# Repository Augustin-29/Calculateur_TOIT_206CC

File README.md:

# Calculateur TOIT 206CC (Version 1)

Ce projet open-source consiste en la rétro-ingénierie et la conception d'un calculateur de remplacement sur mesure pour la gestion du toit escamotable d'une Peugeot 206 CC. La V1 s'appuie sur une architecture matérielle moderne et un système d'exploitation temps réel pour piloter de manière fiable et sécurisée le cycle d'ouverture/fermeture du toit.

---

## 🛠️ Architecture du Projet

Le dépôt regroupe l'ensemble du projet dans une structure centralisée :
*   **`CAO/`** : Conception matérielle complète sous KiCad (Schématiques, empreintes spécifiques, modélisations 3D et fichiers de fabrication Gerber).
*   **`CODE_CT_V1/`** : Logiciel embarqué développé en C/C++ avec une structure de build basée sur CMake.

---

## 💾 Spécifications Techniques (Hardware)

Le module remplace l'électronique d'origine en modernisant la chaîne de traitement et de commande.

*   **Microcontrôleur principal** : STM32F103 (Cortex-M3), choisi pour sa gestion des périphériques et ses timers avancés nécessaires à l'acquisition des capteurs de position.
*   **Interface Véhicule & Diagnostic** : Support de la ligne K (K-line) pour la communication de diagnostic et l'analyse de protocole.
*   **Connectique d'Origine** : Intégration sur le PCB d'une empreinte sur mesure pour le connecteur jaune 26 broches spécifique au faisceau habitacle de la 206 CC.
*   **Routage & Puissance** : 
    *   Routage optimisé des pistes de puissance pour la gestion des courants des moteurs de pompe hydraulique et des actionneurs.
    *   Protection renforcée de l'étage d'alimentation face aux contraintes du réseau électrique automobile (transitoires, variations de tension).
    *   Isolation et conditionnement des signaux des micro-contacts (capteurs de fin de course des éléments du toit et du coffre).

---

## 💻 Logiciel Embarqué (Firmware)

Le code est architecturé pour garantir le déterminisme et la sécurité lors des mouvements mécaniques du toit.

*   **Système d'Exploitation** : Intégration de **FreeRTOS** pour orchestrer les tâches concurrentes (gestion de la machine d'état du toit, scrutation des capteurs, communications).
*   **Gestion de la Sécurité** : Tâches prioritaires surveillant en temps réel l'état des capteurs pour interrompre immédiatement le cycle en cas d'anomalie ou d'obstacle.
*   **Environnement de Développement** : Configuration complète sous **CMake**, facilitant la cross-compilation avec la chaîne d'outils `gcc-arm-none-eabi`.

---

## 📂 Contenu du dossier CAO

Le dossier de conception électronique inclut :
*   Le schéma structurel (`.kicad_sch`) et le routage du PCB (`.kicad_pcb`).
*   Les fichiers de fabrication indispensables (Générés dans `CAO/gerber/` : couches de cuivre, masques de soudure, sérigraphies et fichiers de perçage `.drl`).
*   Les modèles 3D des composants spécifiques (relais automobiles, connecteur jaune 26P, etc.) utilisés pour valider l'intégration mécanique de la carte dans son boîtier.

---

## 🚀 À venir (Roadmap V2)

*   Validation de la machine d'état sur banc de test et intégration véhicule.
*

---
*Projet développé par Augustin — 2026.*

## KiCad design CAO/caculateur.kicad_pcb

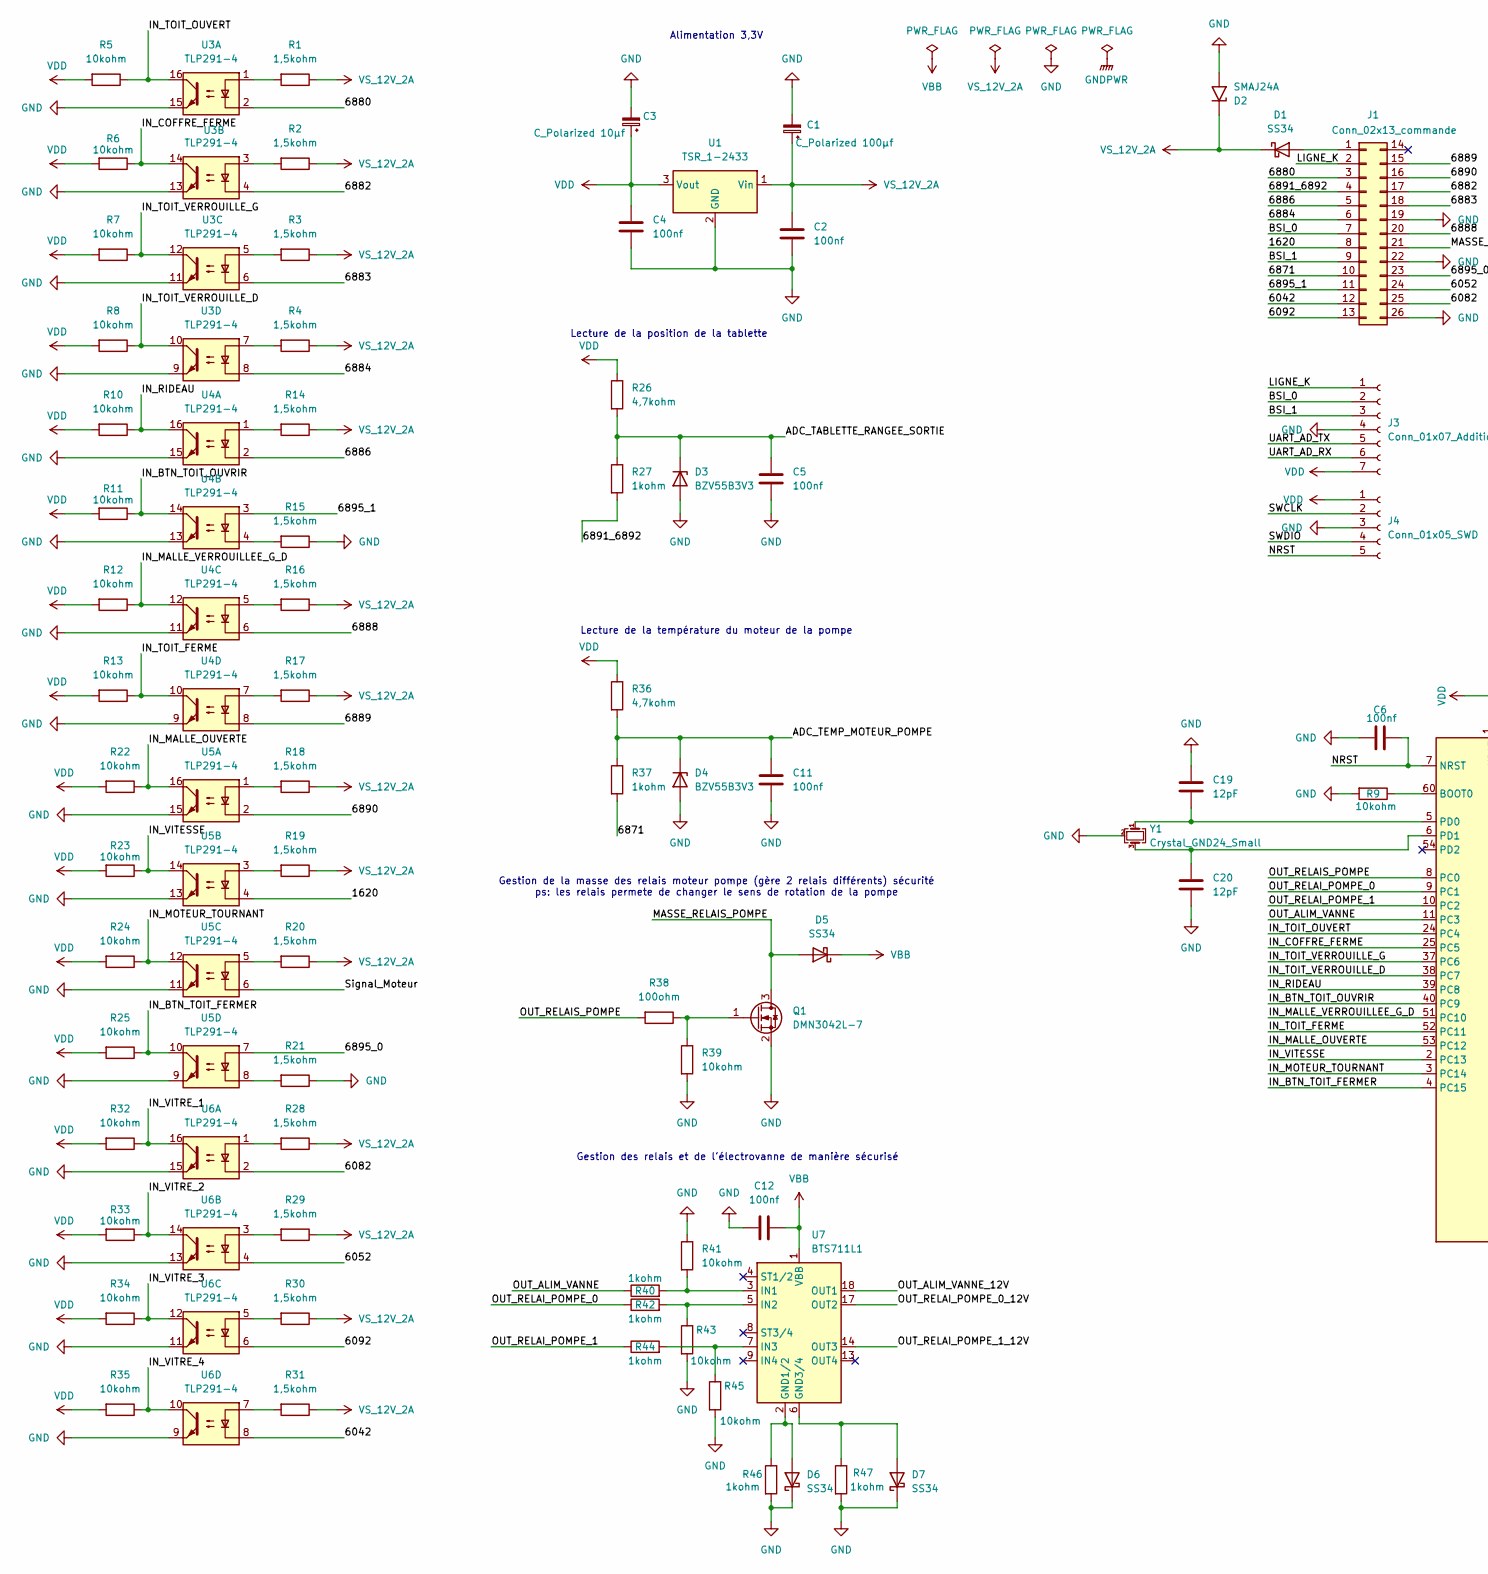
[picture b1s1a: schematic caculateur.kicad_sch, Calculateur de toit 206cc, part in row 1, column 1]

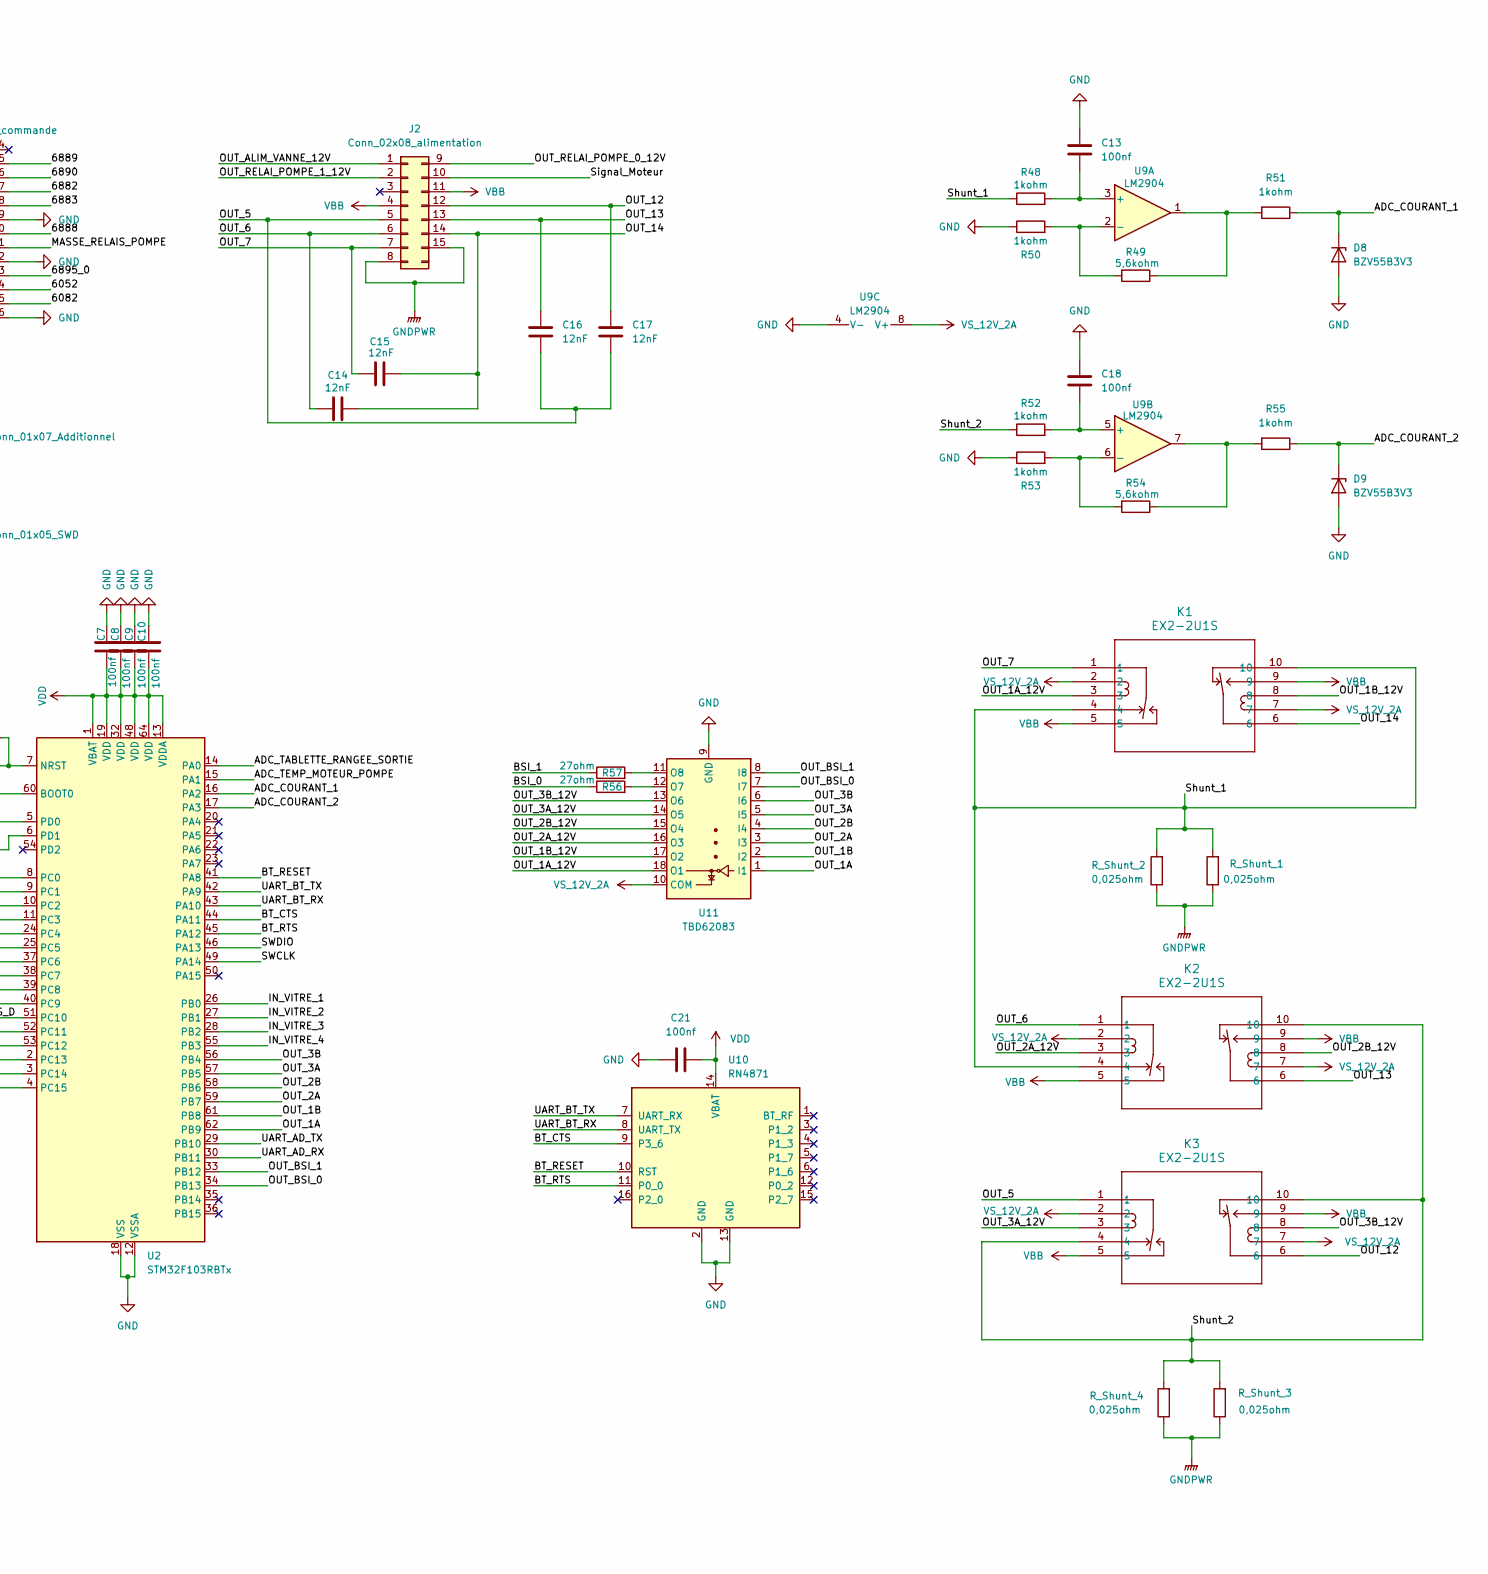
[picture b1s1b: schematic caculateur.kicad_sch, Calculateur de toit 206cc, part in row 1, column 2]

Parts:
C1: C_Polarized 100µf; CP_Elec_10x10
C2, C4, C5, C6, C7, C8, C9, C10, C11, C12, C13, C18, C21: 100nf; C_0805_2012Metric_Pad1.18x1.45mm_HandSolder
C3: C_Polarized 10µf; CP_EIA-3216-18_Kemet-A_HandSolder
C14, C15, C16, C17: 12nF; C_1206_3216Metric
C19, C20: 12pF; C_0805_2012Metric_Pad1.18x1.45mm_HandSolder
D1, D5, D6, D7: SS34; D_SMA
D2: SMAJ24A; D_SMA
D3, D4, D8, D9: BZV55B3V3; D_MiniMELF
J1: Conn_02x13_commande; Connecteur_Jaune_206CC_26P
J2: Conn_02x08_alimentation; Connecteur_Jaune_206CC_15P
J3: Conn_01x07_Additionnel; Hirose_FH12-8S-0.5SH_1x08-1MP_P0.50mm_Horizontal
J4: Conn_01x05_SWD; Tag-Connect_TC2030-IDC-NL_2x03_P1.27mm_Vertical
K1, K2, K3: EX2-2U1S; EX2_NEC
Q1: DMN3042L-7; SOT-23
R1, R2, R3, R4, R14, R15, R16, R17, R18, R19, R20, R21, R28, R29, R30, R31: 1,5kohm; R_0805_2012Metric_Pad1.20x1.40mm_HandSolder
R5, R6, R7, R8, R9, R10, R11, R12, R13, R22, R23, R24, R25, R32, R33, R34, R35, R39, R41, R43, R45: 10kohm; R_0805_2012Metric_Pad1.20x1.40mm_HandSolder
R26, R36: 4,7kohm; R_0805_2012Metric_Pad1.20x1.40mm_HandSolder
R27, R37: 1kohm; R_1206_3216Metric
R38: 100ohm; R_0805_2012Metric_Pad1.20x1.40mm_HandSolder
R40, R42, R44, R46, R47, R48, R50, R51, R52, R53, R55: 1kohm; R_0805_2012Metric_Pad1.20x1.40mm_HandSolder
R49, R54: 5,6kohm; R_0805_2012Metric_Pad1.20x1.40mm_HandSolder
R56, R57: 27ohm; R_1206_3216Metric
R_Shunt_1, R_Shunt_2, R_Shunt_3, R_Shunt_4: 0,025ohm; R_Shunt_Vishay_WSR2_WSR3
U1: TSR_1-2433; Converter_DCDC_TRACO_TSR-1_THT
U2: STM32F103RBTx; LQFP-64_10x10mm_P0.5mm
U3, U4, U5, U6: TLP291-4; SOIC-16_4.55x10.3mm_P1.27mm
U7: BTS711L1; Infineon_SOIC-20W_7.6x12.8mm_P1.27mm
U9: LM2904; SOIC-8_3.9x4.9mm_P1.27mm
U10: RN4871; Microchip_RN4871
U11: TBD62083; SSOP-18_4.4x6.5mm_P0.65mm
Y1: Crystal_GND24_Small; Crystal_SMD_5032-4Pin_5.0x3.2mm

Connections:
/1620: J1.8, U5.4
/6042: J1.12, U6.8
/6052: J1.24, U6.4
/6082: J1.25, U6.2
/6092: J1.13, U6.6
/6871: J1.10, R37.2
/6880: J1.3, U3.2
/6882: J1.17, U3.4
/6883: J1.18, U3.6
/6884: J1.6, U3.8
/6886: J1.5, U4.2
/6888: J1.20, U4.6
/6889: J1.15, U4.8
/6890: J1.16, U5.2
/6891_6892: J1.4, R27.2
/6895_0: J1.23, U5.7
/6895_1: J1.11, U4.3
/ADC_COURANT_1: D8.1 (K), R51.1, U2.16 (PA2)
/ADC_COURANT_2: D9.1 (K), R55.1, U2.17 (PA3)
/ADC_TABLETTE_RANGEE_SORTIE: C5.1, D3.1 (K), R26.2, R27.1, U2.14 (PA0)
/ADC_TEMP_MOTEUR_POMPE: C11.1, D4.1 (K), R36.2, R37.1, U2.15 (PA1)
/BSI_0: J1.7, J3.2, R56.1
/BSI_1: J1.9, J3.3, R57.1
/BT_CTS: U2.44 (PA11), U10.9 (P3_6)
/BT_RESET: U2.41 (PA8), U10.10 (RST)
/BT_RTS: U2.45 (PA12), U10.11 (P0_0)
/IN_BTN_TOIT_FERMER: R25.1, U2.4 (PC15), U5.10
/IN_BTN_TOIT_OUVRIR: R11.1, U2.40 (PC9), U4.14
/IN_COFFRE_FERME: R6.1, U2.25 (PC5), U3.14
/IN_MALLE_OUVERTE: R22.1, U2.53 (PC12), U5.16
/IN_MALLE_VERROUILLEE_G_D: R12.1, U2.51 (PC10), U4.12
/IN_MOTEUR_TOURNANT: R24.1, U2.3 (PC14), U5.12
/IN_RIDEAU: R10.1, U2.39 (PC8), U4.16
/IN_TOIT_FERME: R13.1, U2.52 (PC11), U4.10
/IN_TOIT_OUVERT: R5.1, U2.24 (PC4), U3.16
/IN_TOIT_VERROUILLE_D: R8.1, U2.38 (PC7), U3.10
/IN_TOIT_VERROUILLE_G: R7.1, U2.37 (PC6), U3.12
/IN_VITESSE: R23.1, U2.2 (PC13), U5.14
/IN_VITRE_1: R32.1, U2.26 (PB0), U6.16
/IN_VITRE_2: R33.1, U2.27 (PB1), U6.14
/IN_VITRE_3: R34.1, U2.28 (PB2), U6.12
/IN_VITRE_4: R35.1, U2.55 (PB3), U6.10
/LIGNE_K: J1.2, J3.1
/MASSE_RELAIS_POMPE: D5.2 (A), J1.21, Q1.3 (D)
/NRST: C6.1, J4.5, U2.7 (NRST)
/OUT_1A: U2.62 (PB9), U11.1 (I1)
/OUT_1A_12V: K1.3, U11.18 (O1)
/OUT_1B: U2.61 (PB8), U11.2 (I2)
/OUT_1B_12V: K1.8, U11.17 (O2)
/OUT_2A: U2.59 (PB7), U11.3 (I3)
/OUT_2A_12V: K2.3, U11.16 (O3)
/OUT_2B: U2.58 (PB6), U11.4 (I4)
/OUT_2B_12V: K2.8, U11.15 (O4)
/OUT_3A: U2.57 (PB5), U11.5 (I5)
/OUT_3A_12V: K3.3, U11.14 (O5)
/OUT_3B: U2.56 (PB4), U11.6 (I6)
/OUT_3B_12V: K3.8, U11.13 (O6)
/OUT_5: C16.2, C17.2, J2.5, K3.1
/OUT_6: C14.2, J2.6, K2.1
/OUT_7: C15.2, J2.7, K1.1
/OUT_12: C17.1, J2.12, K3.6
/OUT_13: C16.1, J2.13, K2.6
/OUT_14: C14.1, C15.1, J2.14, K1.6
/OUT_ALIM_VANNE: R40.1, U2.11 (PC3)
/OUT_ALIM_VANNE_12V: J2.1, U7.18 (OUT1)
/OUT_BSI_0: U2.34 (PB13), U11.7 (I7)
/OUT_BSI_1: U2.33 (PB12), U11.8 (I8)
/OUT_RELAIS_POMPE: R38.2, U2.8 (PC0)
/OUT_RELAI_POMPE_0: R42.1, U2.9 (PC1)
/OUT_RELAI_POMPE_0_12V: J2.9, U7.17 (OUT2)
/OUT_RELAI_POMPE_1: R44.1, U2.10 (PC2)
/OUT_RELAI_POMPE_1_12V: J2.2, U7.14 (OUT3)
/SWCLK: J4.2, U2.49 (PA14)
/SWDIO: J4.4, U2.46 (PA13)
/Shunt_1: K1.4, K1.10, K2.4, R48.1, R_Shunt_1.2, R_Shunt_2.2
/Shunt_2: K2.10, K3.4, K3.10, R52.1, R_Shunt_3.2, R_Shunt_4.2
/Signal_Moteur: J2.10, U5.6
/UART_AD_RX: J3.6, U2.30 (PB11)
/UART_AD_TX: J3.5, U2.29 (PB10)
/UART_BT_RX: U2.43 (PA10), U10.8 (UART_TX)
/UART_BT_TX: U2.42 (PA9), U10.7 (UART_RX)
GND: C1.2, C2.2, C3.2, C4.2, C5.2, C6.2, C7.2, C8.2, C9.2, C10.2, C11.2, C12.2, C13.1, C18.1, C19.1, C20.2, C21.2, D2.2 (A2), D3.2 (A), D4.2 (A), D6.1 (K), D7.1 (K), D8.2 (A), D9.2 (A), J1.19, J1.22, J1.26, J3.4, J4.3, Q1.2 (S), R9.2, R15.1, R21.1, R39.2, R41.1, R43.2, R45.2, R46.2, R47.2, R50.1, R53.1, U1.2 (GND), U2.12 (VSSA), U2.18 (VSS), U2.31 (VSS), U2.47 (VSS), U2.63 (VSS), U3.9, U3.11, U3.13, U3.15, U4.9, U4.11, U4.13, U4.15, U5.9, U5.11, U5.13, U5.15, U6.9, U6.11, U6.13, U6.15, U9.4 (V-), U10.2 (GND), U10.13 (GND), U11.9 (GND), Y1.2 (G), Y1.4 (G)
GNDPWR: J2.8, J2.15, R_Shunt_1.1, R_Shunt_2.1, R_Shunt_3.1, R_Shunt_4.1
unnamed: D1.2 (A), J1.1
unnamed: D6.2 (A), R46.1, U7.2 (GND1/2)
unnamed: D7.2 (A), R47.1, U7.6 (GND3/4)
unnamed: Q1.1 (G), R38.1, R39.1
unnamed: R1.2, U3.1
unnamed: R2.2, U3.3
unnamed: R3.2, U3.5
unnamed: R4.2, U3.7
unnamed: R14.2, U4.1
unnamed: R15.2, U4.4
unnamed: R16.2, U4.5
unnamed: R17.2, U4.7
unnamed: R18.2, U5.1
unnamed: R19.2, U5.3
unnamed: R20.2, U5.5
unnamed: R21.2, U5.8
unnamed: R28.2, U6.1
unnamed: R29.2, U6.3
unnamed: R30.2, U6.5
unnamed: R31.2, U6.7
unnamed: R49.1, R51.2, U9.1
unnamed: R54.1, R55.2, U9.7
unnamed: R9.1, U2.60 (BOOT0)
unnamed: C19.2, U2.5 (PD0), Y1.1
unnamed: C20.1, U2.6 (PD1), Y1.3
unnamed: R40.2, R41.2, U7.3 (IN1)
unnamed: R42.2, R43.1, U7.5 (IN2)
unnamed: R44.2, R45.1, U7.7 (IN3)
unnamed: C13.2, R48.2, U9.3 (+)
unnamed: R49.2, R50.2, U9.2 (-)
unnamed: C18.2, R52.2, U9.5 (+)
unnamed: R53.2, R54.2, U9.6 (-)
unnamed: R56.2, U11.12 (O7)
unnamed: R57.2, U11.11 (O8)

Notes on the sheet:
Gestion de la masse des relais moteur pompe (gère 2 relais différents) sécurité ps: les relais permete de changer le sens de rotation de la pompe
Lecture de la température du moteur de la pompe
Alimentation 3,3V
Gestion des relais et de l'électrovanne de manière sécurisé
Lecture de la position de la tablette

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
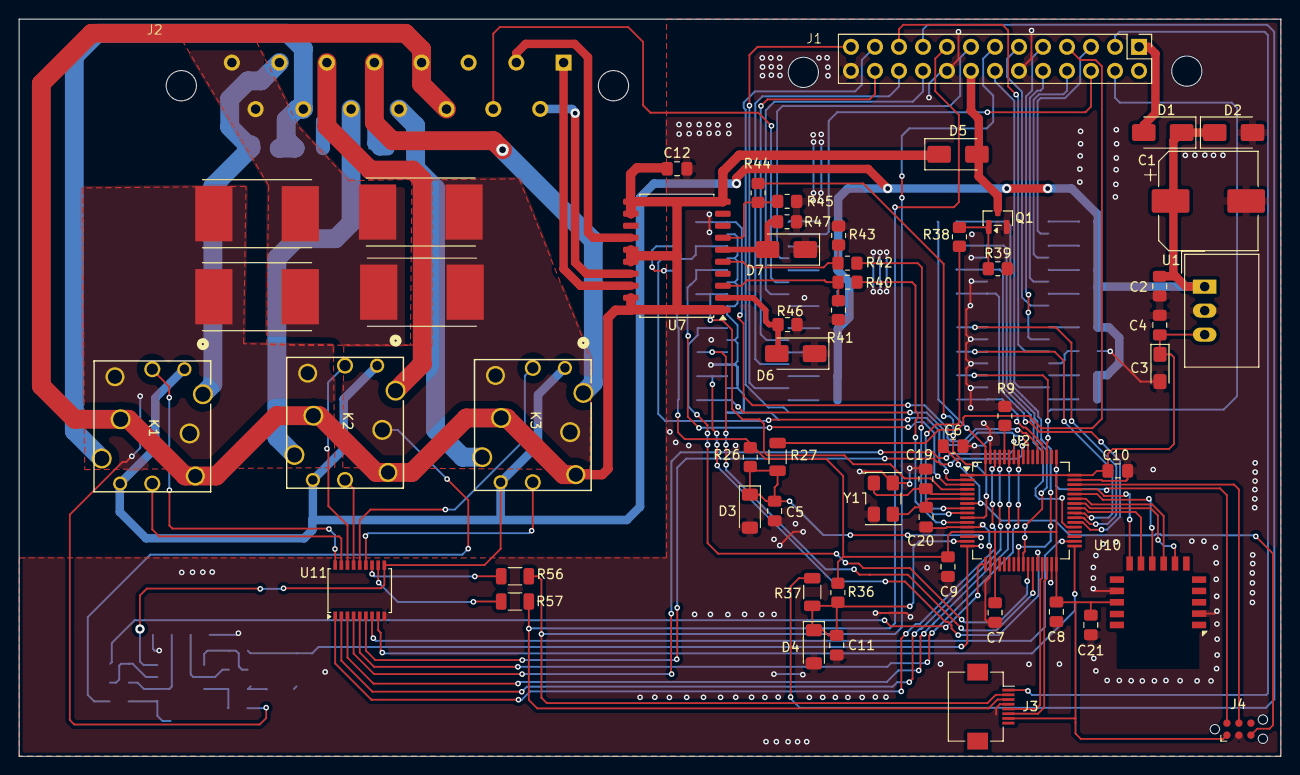
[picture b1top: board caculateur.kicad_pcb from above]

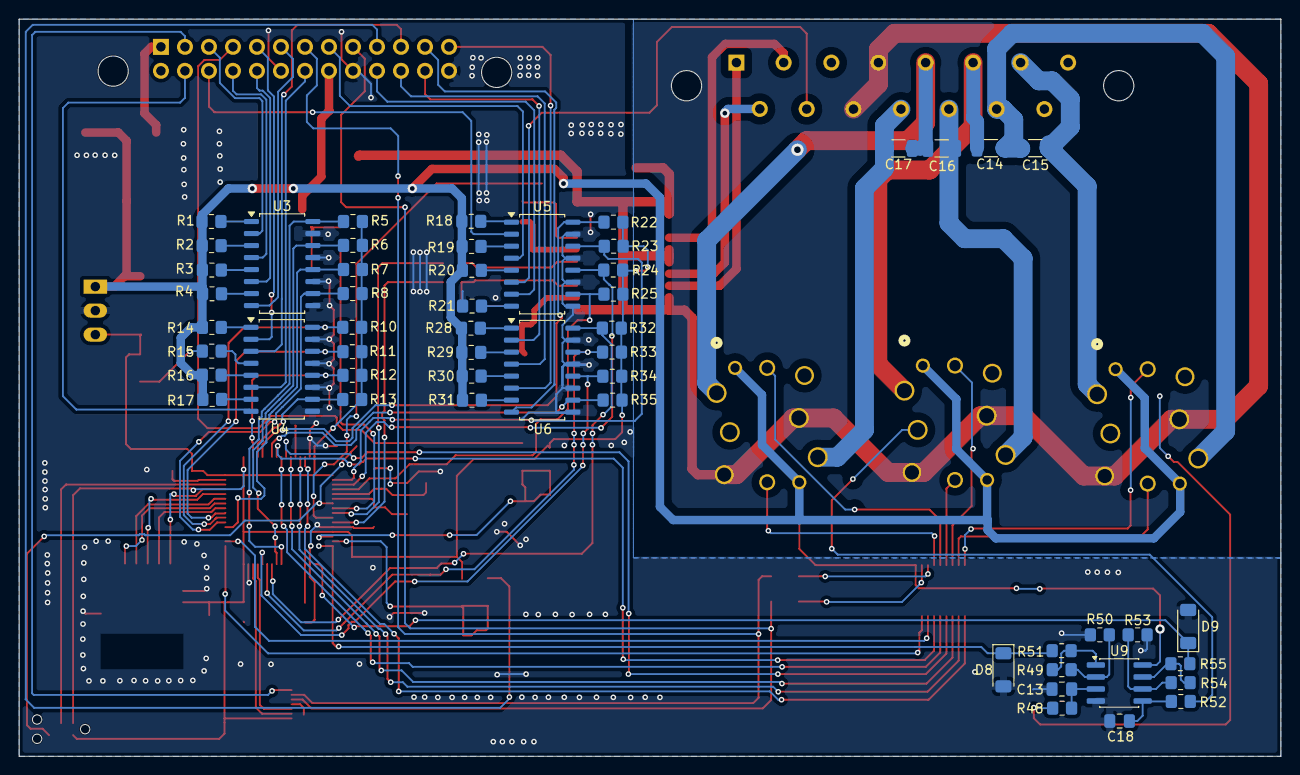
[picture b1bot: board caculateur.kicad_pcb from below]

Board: 2 copper layers, 133.5 x 78.0 mm, 110 parts (53 on the bottom side), 120 nets.

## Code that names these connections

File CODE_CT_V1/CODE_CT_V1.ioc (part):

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Mcu.Name=STM32F103R(8-B)Tx
Mcu.Package=LQFP64
Mcu.UserName=STM32F103RBTx
PA0-WKUP.GPIOParameters=GPIO_Label
PA0-WKUP.GPIO_Label=ADC_TABLETTE_RANGEE_SORTIE
PA0-WKUP.Signal=ADCx_IN0
PA1.GPIOParameters=GPIO_Label
PA1.GPIO_Label=ADC_TEMP_MOTEUR_POMPE
PA1.Signal=ADCx_IN1
PA10.GPIOParameters=GPIO_Label
PA10.GPIO_Label=UART_BT_RX
PA10.Mode=Asynchronous
PA10.Signal=USART1_RX
PA11.GPIOParameters=GPIO_Label
PA11.GPIO_Label=UART_BT_CTS
PA11.Mode=CTS_RTS
PA11.Signal=USART1_CTS
PA12.GPIOParameters=GPIO_Label
PA12.GPIO_Label=UART_BT_RTS
PA12.Mode=CTS_RTS
PA12.Signal=USART1_RTS
PA13.Mode=Serial_Wire
PA13.Signal=SYS_JTMS-SWDIO
PA14.Mode=Serial_Wire
PA14.Signal=SYS_JTCK-SWCLK
PA2.GPIOParameters=GPIO_Label
PA2.GPIO_Label=ADC_COURANT_1
PA2.Signal=ADCx_IN2
PA3.GPIOParameters=GPIO_Label
PA3.GPIO_Label=ADC_COURANT_2
PA3.Signal=ADCx_IN3
PA8.GPIOParameters=GPIO_Label
PA8.GPIO_Label=BT_RESET
PA8.Signal=GPIO_Output
PA9.GPIOParameters=GPIO_Label
PA9.GPIO_Label=UART_BT_TX
PA9.Mode=Asynchronous
PA9.Signal=USART1_TX
PB0.GPIOParameters=GPIO_Label
PB0.GPIO_Label=IN_VITRE_1
PB0.Signal=GPIO_Input
PB1.GPIOParameters=GPIO_Label
PB1.GPIO_Label=IN_VITRE_2
PB1.Signal=GPIO_Input
PB10.GPIOParameters=GPIO_Label
PB10.GPIO_Label=UART_AD_TX
PB10.Mode=Asynchronous
PB10.Signal=USART3_TX
PB11.GPIOParameters=GPIO_Label
PB11.GPIO_Label=UART_AD_RX
PB11.Mode=Asynchronous
PB11.Signal=USART3_RX
PB12.GPIOParameters=GPIO_Label
PB12.GPIO_Label=OUT_BSI_1
PB12.Signal=GPIO_Output
PB13.GPIOParameters=GPIO_Label
PB13.GPIO_Label=OUT_BSI_0
PB13.Signal=GPIO_Output
PB2.GPIOParameters=GPIO_Label
PB2.GPIO_Label=IN_VITRE_3
PB2.Signal=GPIO_Input
PB3.GPIOParameters=GPIO_Label
PB3.GPIO_Label=IN_VITRE_4
PB3.Signal=GPIO_Input
PB4.GPIOParameters=GPIO_Label
PB4.GPIO_Label=OUT_3B
PB4.Signal=GPIO_Output
PB5.GPIOParameters=GPIO_Label
PB5.GPIO_Label=OUT_3A
PB5.Signal=GPIO_Output
PB6.GPIOParameters=GPIO_Label
PB6.GPIO_Label=OUT_2B
PB6.Signal=GPIO_Output
PB7.GPIOParameters=GPIO_Label
PB7.GPIO_Label=OUT_2A
PB7.Signal=GPIO_Output
PB8.GPIOParameters=GPIO_Label
PB8.GPIO_Label=OUT_1B
PB8.Signal=GPIO_Output
PB9.GPIOParameters=GPIO_Label
PB9.GPIO_Label=OUT_1A
PB9.Signal=GPIO_Output
PC0.GPIOParameters=GPIO_Label
PC0.GPIO_Label=OUT_RELAIS_POMPE
PC0.Signal=GPIO_Output
PC1.GPIOParameters=GPIO_Label
PC1.GPIO_Label=OUT_RELAI_POMPE_0
PC1.Signal=GPIO_Output
PC10.GPIOParameters=GPIO_Label
PC10.GPIO_Label=IN_MALLE_VERROUILLEE_G_D
PC10.Signal=GPIO_Input
PC11.GPIOParameters=GPIO_Label
PC11.GPIO_Label=IN_TOIT_FERME
PC11.Signal=GPIO_Input
PC12.GPIOParameters=GPIO_Label
PC12.GPIO_Label=IN_MALLE_OUVERTE
PC12.Signal=GPIO_Input
PC13-TAMPER-RTC.GPIOParameters=GPIO_Label
PC13-TAMPER-RTC.GPIO_Label=IN_VITESSE
PC13-TAMPER-RTC.Signal=GPIO_Input
PC14-OSC32_IN.GPIOParameters=GPIO_Label
PC14-OSC32_IN.GPIO_Label=IN_MOTEUR_TOURNANT
PC14-OSC32_IN.Signal=GPIO_Input
PC15-OSC32_OUT.GPIOParameters=GPIO_Label
PC15-OSC32_OUT.GPIO_Label=IN_BTN_TOIT_FERMER
PC15-OSC32_OUT.Signal=GPIO_Input
PC2.GPIOParameters=GPIO_Label
PC2.GPIO_Label=OUT_RELAI_POMPE_1
PC2.Signal=GPIO_Output
PC3.GPIOParameters=GPIO_Label
PC3.GPIO_Label=OUT_ALIM_VANNE
PC3.Signal=GPIO_Output
PC4.GPIOParameters=GPIO_Label
PC4.GPIO_Label=IN_TOIT_OUVERT
PC4.Signal=GPIO_Input
PC5.GPIOParameters=GPIO_Label
PC5.GPIO_Label=IN_COFFRE_FERME
PC5.Signal=GPIO_Input
PC6.GPIOParameters=GPIO_Label
PC6.GPIO_Label=IN_TOIT_VERROUILLE_G
PC6.Signal=GPIO_Input
PC7.GPIOParameters=GPIO_Label
PC7.GPIO_Label=IN_TOIT_VERROUILLE_D
PC7.Signal=GPIO_Input
PC8.GPIOParameters=GPIO_Label
PC8.GPIO_Label=IN_RIDEAU
PC8.Signal=GPIO_Input
PC9.GPIOParameters=GPIO_Label
PC9.GPIO_Label=IN_BTN_TOIT_OUVRIR
PC9.Signal=GPIO_Input
PD0-OSC_IN.Mode=HSE-External-Oscillator
PD0-OSC_IN.Signal=RCC_OSC_IN
PD1-OSC_OUT.Mode=HSE-External-Oscillator
PD1-OSC_OUT.Signal=RCC_OSC_OUT
RCC.SYSCLKFreq_VALUE=72000000
RCC.SYSCLKSource=RCC_SYSCLKSOURCE_PLLCLK
board=custom

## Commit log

2026-06-27 Premier commit : ajout de toute la structure
2026-06-27 Correction : Intégration complète du code et de l'historique CAO
2026-06-27 Add initial README for TOIT 206CC project
    This README provides an overview of the TOIT 206CC project, detailing its architecture, technical specifications, firmware, and future roadmap.
2026-06-27 Sauvegarde de la configuration VS Code et Workspace
